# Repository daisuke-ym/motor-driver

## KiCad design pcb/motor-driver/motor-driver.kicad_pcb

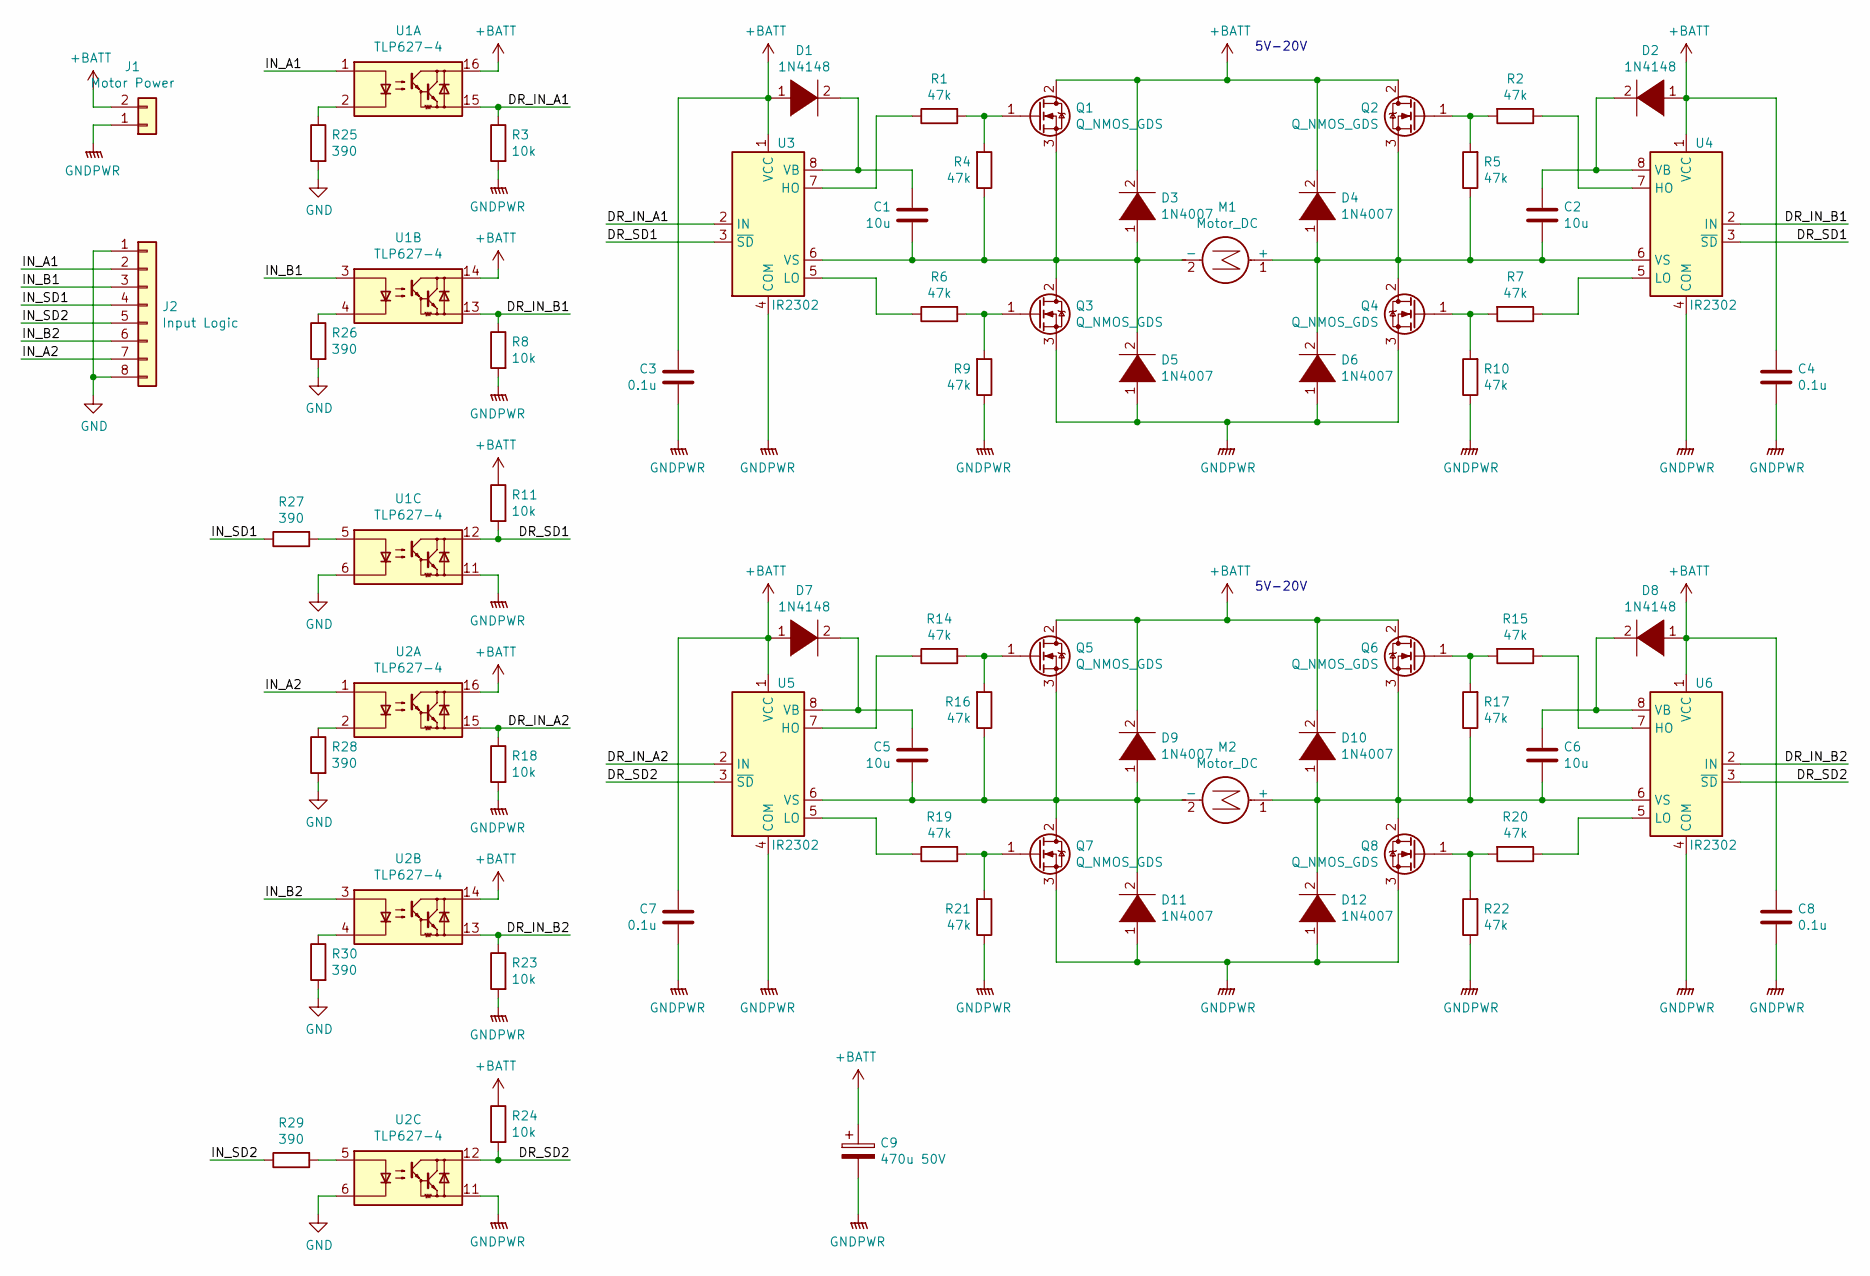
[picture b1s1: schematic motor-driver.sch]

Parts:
C1, C2, C5, C6: 10u; C_Disc_D6.0mm_W4.4mm_P5.00mm
C3, C4, C7, C8: 0.1u; C_Disc_D5.0mm_W2.5mm_P2.50mm
C9: 470u 50V; CP_Radial_D12.5mm_P5.00mm
D1, D2, D7, D8: 1N4148; D_DO-35_SOD27_P2.54mm_Vertical_KathodeUp
D3, D4, D5, D6, D9, D10, D11, D12: 1N4007; D_DO-41_SOD81_P2.54mm_Vertical_KathodeUp
J1: Motor Power; PhoenixContact_MSTBVA_2,5_2-G-5,08_1x02_P5.08mm_Vertical
J2: Input Logic; PinHeader_1x08_P2.54mm_Vertical
M1, M2: Motor_DC; PhoenixContact_MSTBVA_2,5_2-G-5,08_1x02_P5.08mm_Vertical
Q1, Q2, Q3, Q4, Q5, Q6, Q7, Q8: Q_NMOS_GDS; TO-220-3_Vertical
R1, R2, R4, R5, R6, R7, R9, R10, R14, R15, R16, R17, R19, R20, R21, R22: 47k; R_Axial_DIN0207_L6.3mm_D2.5mm_P2.54mm_Vertical
R3, R8, R11, R18, R23, R24: 10k; R_Axial_DIN0207_L6.3mm_D2.5mm_P2.54mm_Vertical
R25, R26, R27, R28, R29, R30: 390; R_Axial_DIN0207_L6.3mm_D2.5mm_P2.54mm_Vertical
U1, U2: TLP627-4; DIP-16_W7.62mm
U3, U4, U5, U6: IR2302; DIP-8_W7.62mm

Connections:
+BATT: C3.1, C4.1, C7.1, C8.1, C9.1, D1.1 (K), D2.1 (K), D3.2 (A), D4.2 (A), D7.1 (K), D8.1 (K), D9.2 (A), D10.2 (A), J1.2, Q1.2 (D), Q2.2 (D), Q5.2 (D), Q6.2 (D), R11.1, R24.1, U1.14, U1.16, U2.14, U2.16, U3.1 (VCC), U4.1 (VCC), U5.1 (VCC), U6.1 (VCC)
/DR_IN_A1: R3.1, U1.15, U3.2 (IN)
/DR_IN_A2: R18.1, U2.15, U5.2 (IN)
/DR_IN_B1: R8.1, U1.13, U4.2 (IN)
/DR_IN_B2: R23.1, U2.13, U6.2 (IN)
/DR_SD1: R11.2, U1.12, U3.3 (~SD), U4.3 (~SD)
/DR_SD2: R24.2, U2.12, U5.3 (~SD), U6.3 (~SD)
/IN_A1: J2.2, U1.1
/IN_A2: J2.7, U2.1
/IN_B1: J2.3, U1.3
/IN_B2: J2.6, U2.3
/IN_SD1: J2.4, R27.1
/IN_SD2: J2.5, R29.1
GND: J2.1, J2.8, R25.2, R26.2, R28.2, R30.2, U1.6, U2.6
GNDPWR: C3.2, C4.2, C7.2, C8.2, C9.2, D5.1 (K), D6.1 (K), D11.1 (K), D12.1 (K), J1.1, Q3.3 (S), Q4.3 (S), Q7.3 (S), Q8.3 (S), R3.2, R8.2, R9.1, R10.1, R18.2, R21.1, R22.1, R23.2, U1.11, U2.11, U3.4 (COM), U4.4 (COM), U5.4 (COM), U6.4 (COM)
unnamed: C1.1, D1.2 (A), U3.8 (VB)
unnamed: C1.2, D3.1 (K), D5.2 (A), M1.2 (-), Q1.3 (S), Q3.2 (D), R4.1, U3.6 (VS)
unnamed: C2.1, D2.2 (A), U4.8 (VB)
unnamed: C2.2, D4.1 (K), D6.2 (A), M1.1 (+), Q2.3 (S), Q4.2 (D), R5.1, U4.6 (VS)
unnamed: C5.1, D7.2 (A), U5.8 (VB)
unnamed: C5.2, D9.1 (K), D11.2 (A), M2.2 (-), Q5.3 (S), Q7.2 (D), R16.1, U5.6 (VS)
unnamed: C6.1, D8.2 (A), U6.8 (VB)
unnamed: C6.2, D10.1 (K), D12.2 (A), M2.1 (+), Q6.3 (S), Q8.2 (D), R17.1, U6.6 (VS)
unnamed: Q1.1 (G), R1.2, R4.2
unnamed: Q2.1 (G), R2.2, R5.2
unnamed: Q3.1 (G), R6.2, R9.2
unnamed: Q4.1 (G), R7.2, R10.2
unnamed: Q5.1 (G), R14.2, R16.2
unnamed: Q6.1 (G), R15.2, R17.2
unnamed: Q7.1 (G), R19.2, R21.2
unnamed: Q8.1 (G), R20.2, R22.2
unnamed: R1.1, U3.7 (HO)
unnamed: R2.1, U4.7 (HO)
unnamed: R6.1, U3.5 (LO)
unnamed: R7.1, U4.5 (LO)
unnamed: R14.1, U5.7 (HO)
unnamed: R15.1, U6.7 (HO)
unnamed: R19.1, U5.5 (LO)
unnamed: R20.1, U6.5 (LO)
unnamed: R25.1, U1.2
unnamed: R26.1, U1.4
unnamed: R27.2, U1.5
unnamed: R28.1, U2.2
unnamed: R29.2, U2.5
unnamed: R30.1, U2.4

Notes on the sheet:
5V-20V

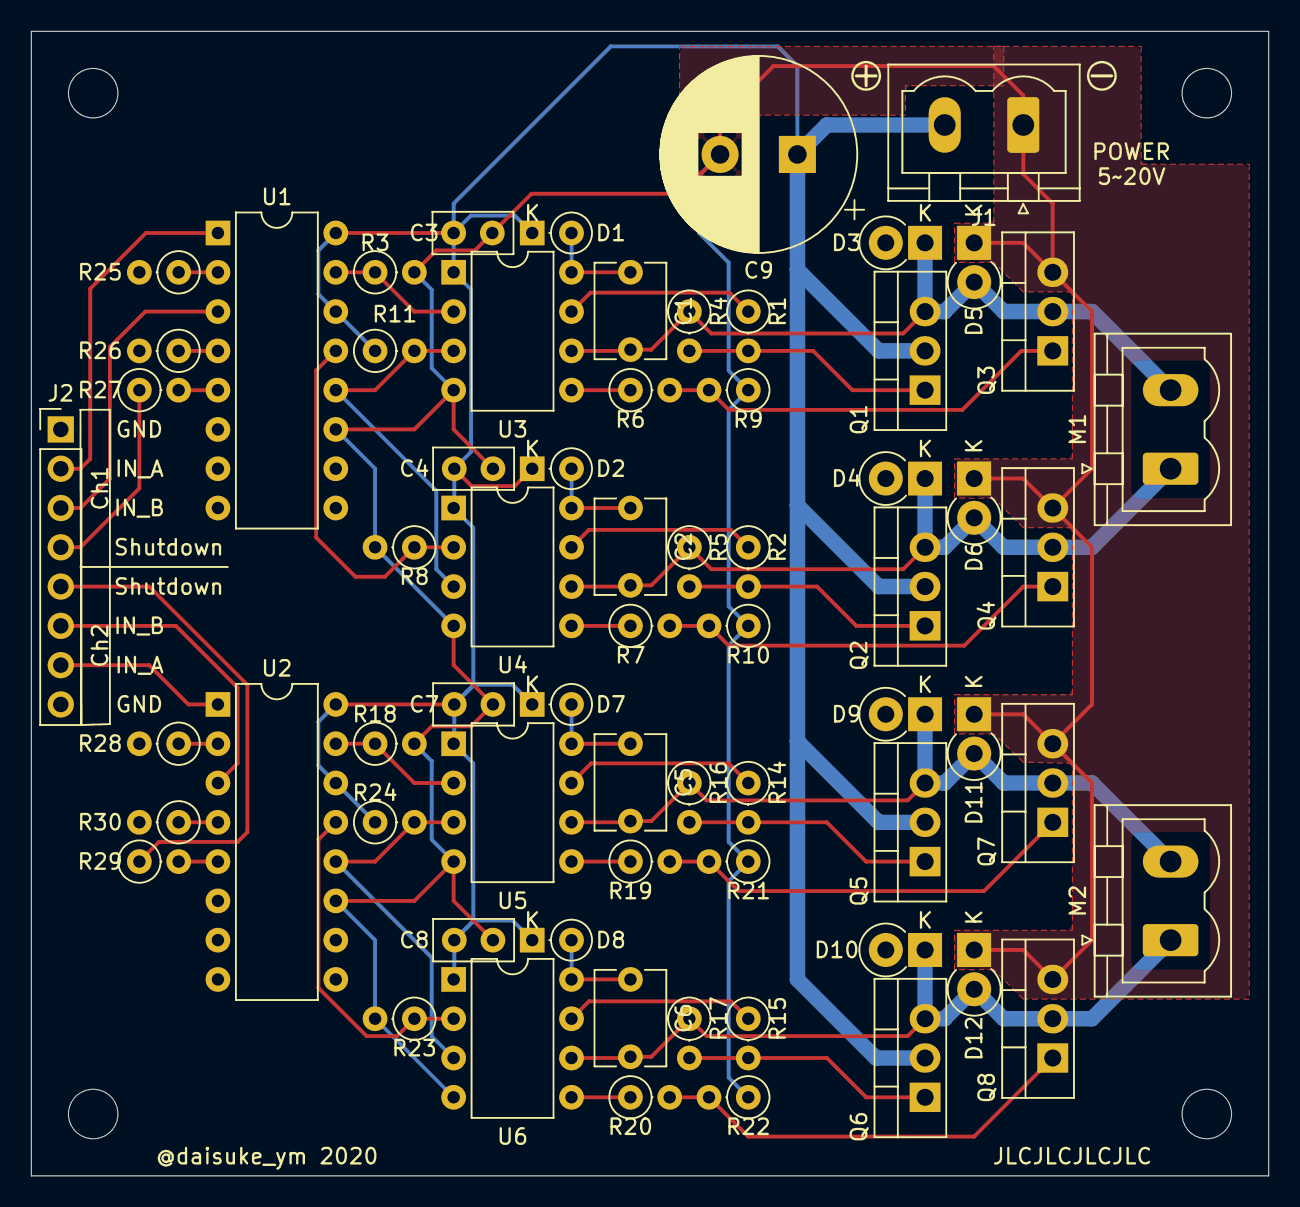
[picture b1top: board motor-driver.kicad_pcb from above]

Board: 2 copper layers, 80.0 x 74.0 mm, 71 parts (0 on the bottom side), 45 nets.

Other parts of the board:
MH1, MH2, MH3, MH4: MountingHole_3.2mm_M3

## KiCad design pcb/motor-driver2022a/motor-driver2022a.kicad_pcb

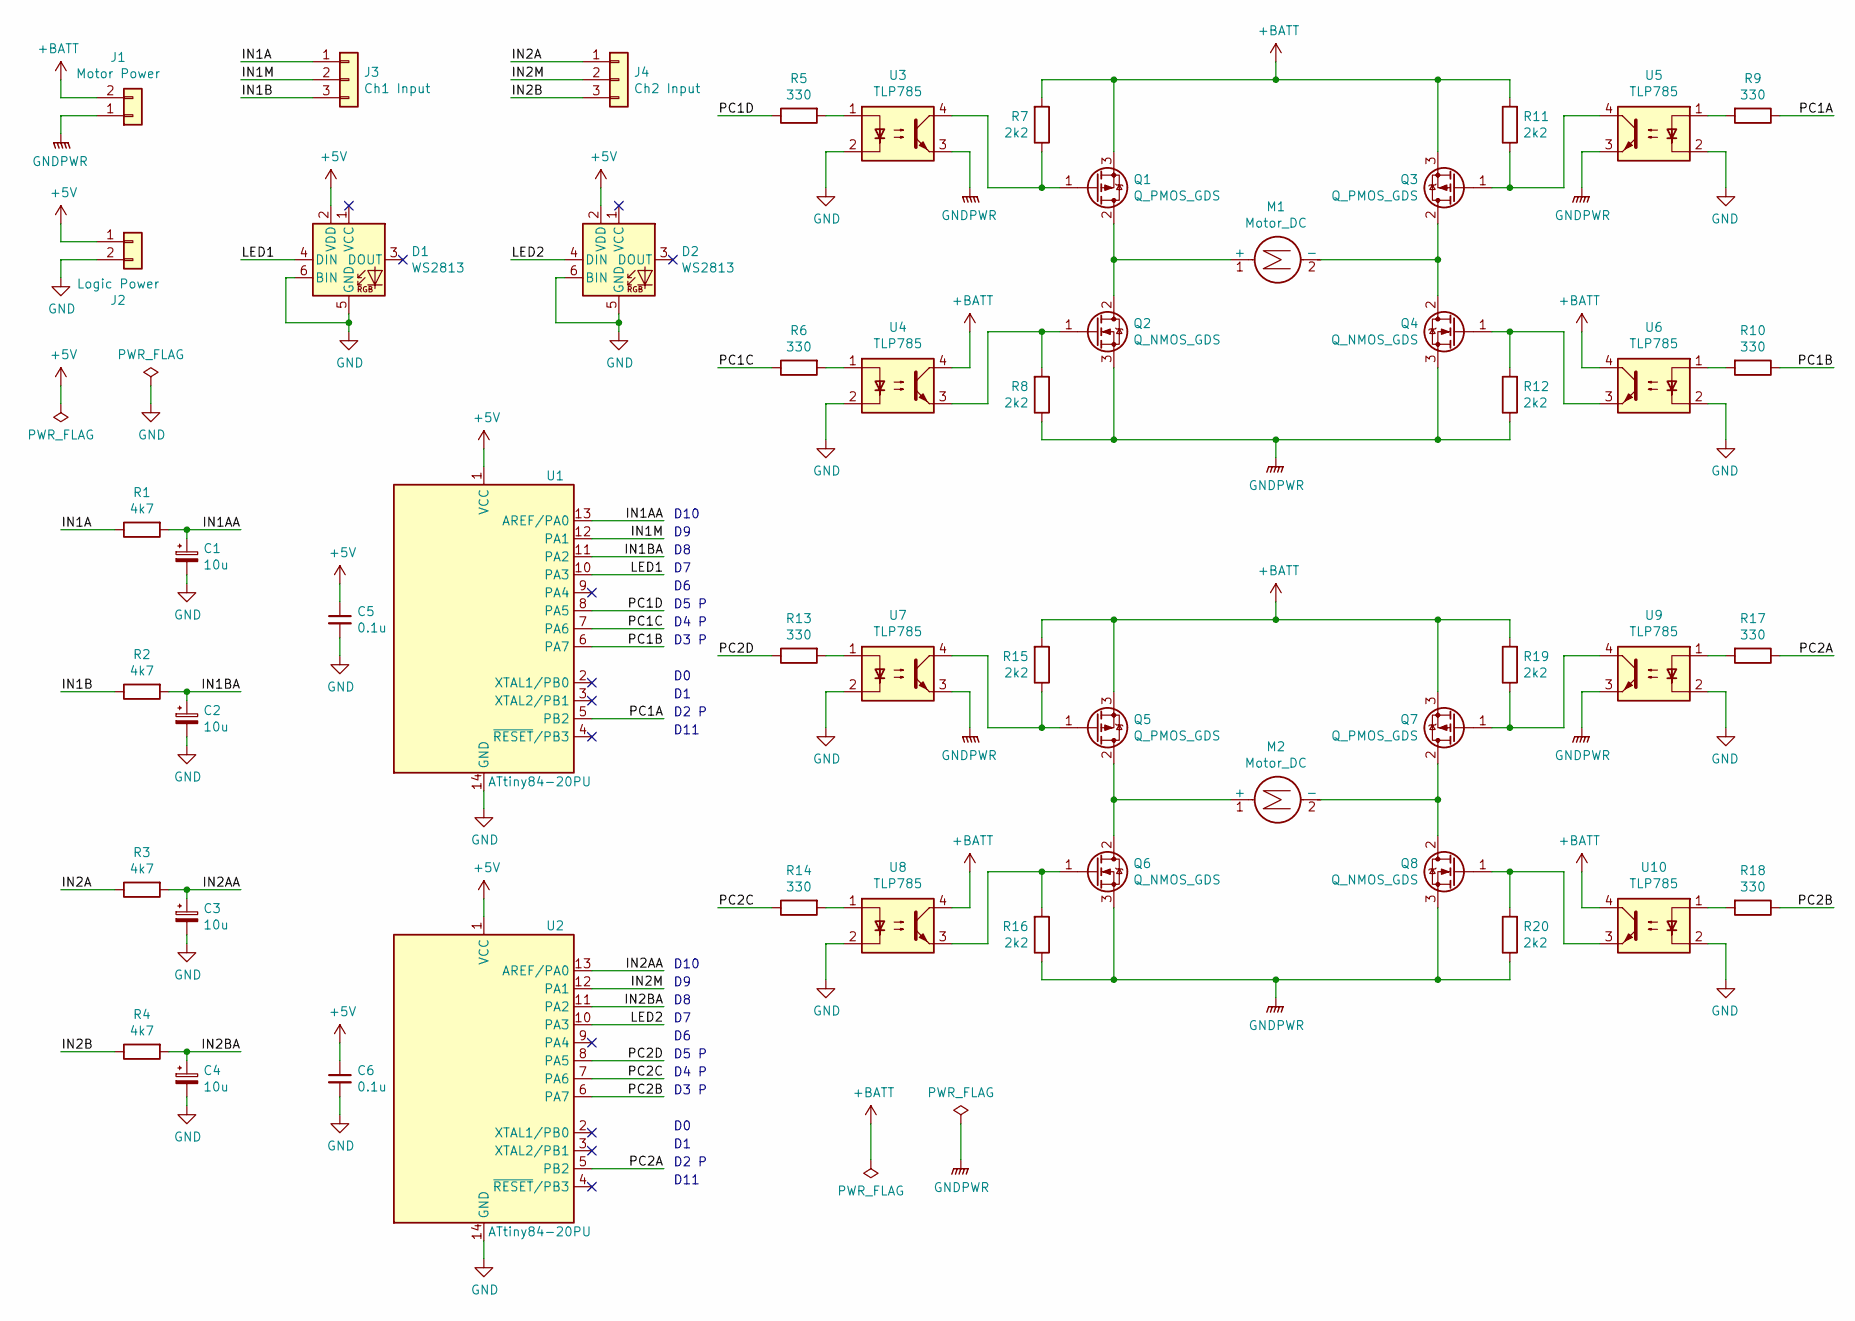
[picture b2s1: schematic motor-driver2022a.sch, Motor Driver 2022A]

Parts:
C1, C2, C3, C4: 10u; CP_Radial_D4.0mm_P1.50mm
C5, C6: 0.1u; C_Disc_D3.0mm_W2.0mm_P2.50mm
D1, D2: WS2813; LED_WS2812_PLCC6_5.0x5.0mm_P1.6mm
J1: Motor Power; AMASS_XT30PW-F_1x02_P2.50mm_Horizontal
J2: Logic Power; PinHeader_1x02_P2.54mm_Horizontal
J3: Ch1 Input; PinHeader_1x03_P2.54mm_Horizontal
J4: Ch2 Input; PinHeader_1x03_P2.54mm_Horizontal
M1, M2: Motor_DC; AMASS_XT30PW-F_1x02_P2.50mm_Horizontal
Q1, Q3, Q5, Q7: Q_PMOS_GDS; TO-220F-3_Vertical
Q2, Q4, Q6, Q8: Q_NMOS_GDS; TO-220F-3_Vertical
R1, R2, R3, R4: 4k7; R_Axial_DIN0207_L6.3mm_D2.5mm_P2.54mm_Vertical
R5, R6, R9, R10, R13, R14, R17, R18: 330; R_Axial_DIN0207_L6.3mm_D2.5mm_P2.54mm_Vertical
R7, R8, R11, R12, R15, R16, R19, R20: 2k2; R_Axial_DIN0207_L6.3mm_D2.5mm_P2.54mm_Vertical
U1, U2: ATtiny84-20PU; DIP-14_W7.62mm
U3, U4, U5, U6, U7, U8, U9, U10: TLP785; DIP-4_W7.62mm

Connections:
+5V: C5.1, C6.1, D1.2 (VDD), D2.2 (VDD), J2.1, U1.1 (VCC), U2.1 (VCC)
+BATT: J1.2, Q1.3 (S), Q3.3 (S), Q5.3 (S), Q7.3 (S), R7.2, R11.2, R15.2, R19.2, U4.4, U6.4, U8.4, U10.4
/IN1A: J3.1, R1.1
/IN1AA: C1.1, R1.2, U1.13 (AREF/PA0)
/IN1B: J3.3, R2.1
/IN1BA: C2.1, R2.2, U1.11 (PA2)
/IN1M: J3.2, U1.12 (PA1)
/IN2A: J4.1, R3.1
/IN2AA: C3.1, R3.2, U2.13 (AREF/PA0)
/IN2B: J4.3, R4.1
/IN2BA: C4.1, R4.2, U2.11 (PA2)
/IN2M: J4.2, U2.12 (PA1)
/LED1: D1.4 (DIN), U1.10 (PA3)
/LED2: D2.4 (DIN), U2.10 (PA3)
/PC1A: R9.1, U1.5 (PB2)
/PC1B: R10.1, U1.6 (PA7)
/PC1C: R6.1, U1.7 (PA6)
/PC1D: R5.1, U1.8 (PA5)
/PC2A: R17.1, U2.5 (PB2)
/PC2B: R18.1, U2.6 (PA7)
/PC2C: R14.1, U2.7 (PA6)
/PC2D: R13.1, U2.8 (PA5)
GND: C1.2, C2.2, C3.2, C4.2, C5.2, C6.2, D1.5 (GND), D1.6 (BIN), D2.5 (GND), D2.6 (BIN), J2.2, U1.14 (GND), U2.14 (GND), U3.2, U4.2, U5.2, U6.2, U7.2, U8.2, U9.2, U10.2
GNDPWR: J1.1, Q2.3 (S), Q4.3 (S), Q6.3 (S), Q8.3 (S), R8.1, R12.1, R16.1, R20.1, U3.3, U5.3, U7.3, U9.3
unnamed: M1.1 (+), Q1.2 (D), Q2.2 (D)
unnamed: M1.2 (-), Q3.2 (D), Q4.2 (D)
unnamed: M2.1 (+), Q5.2 (D), Q6.2 (D)
unnamed: M2.2 (-), Q7.2 (D), Q8.2 (D)
unnamed: Q1.1 (G), R7.1, U3.4
unnamed: Q2.1 (G), R8.2, U4.3
unnamed: Q3.1 (G), R11.1, U5.4
unnamed: Q4.1 (G), R12.2, U6.3
unnamed: Q5.1 (G), R15.1, U7.4
unnamed: Q6.1 (G), R16.2, U8.3
unnamed: Q7.1 (G), R19.1, U9.4
unnamed: Q8.1 (G), R20.2, U10.3
unnamed: R5.2, U3.1
unnamed: R6.2, U4.1
unnamed: R9.2, U5.1
unnamed: R10.2, U6.1
unnamed: R13.2, U7.1
unnamed: R14.2, U8.1
unnamed: R17.2, U9.1
unnamed: R18.2, U10.1

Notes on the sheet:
D10
D4 P
D3 P
D2 P
D5 P
D11

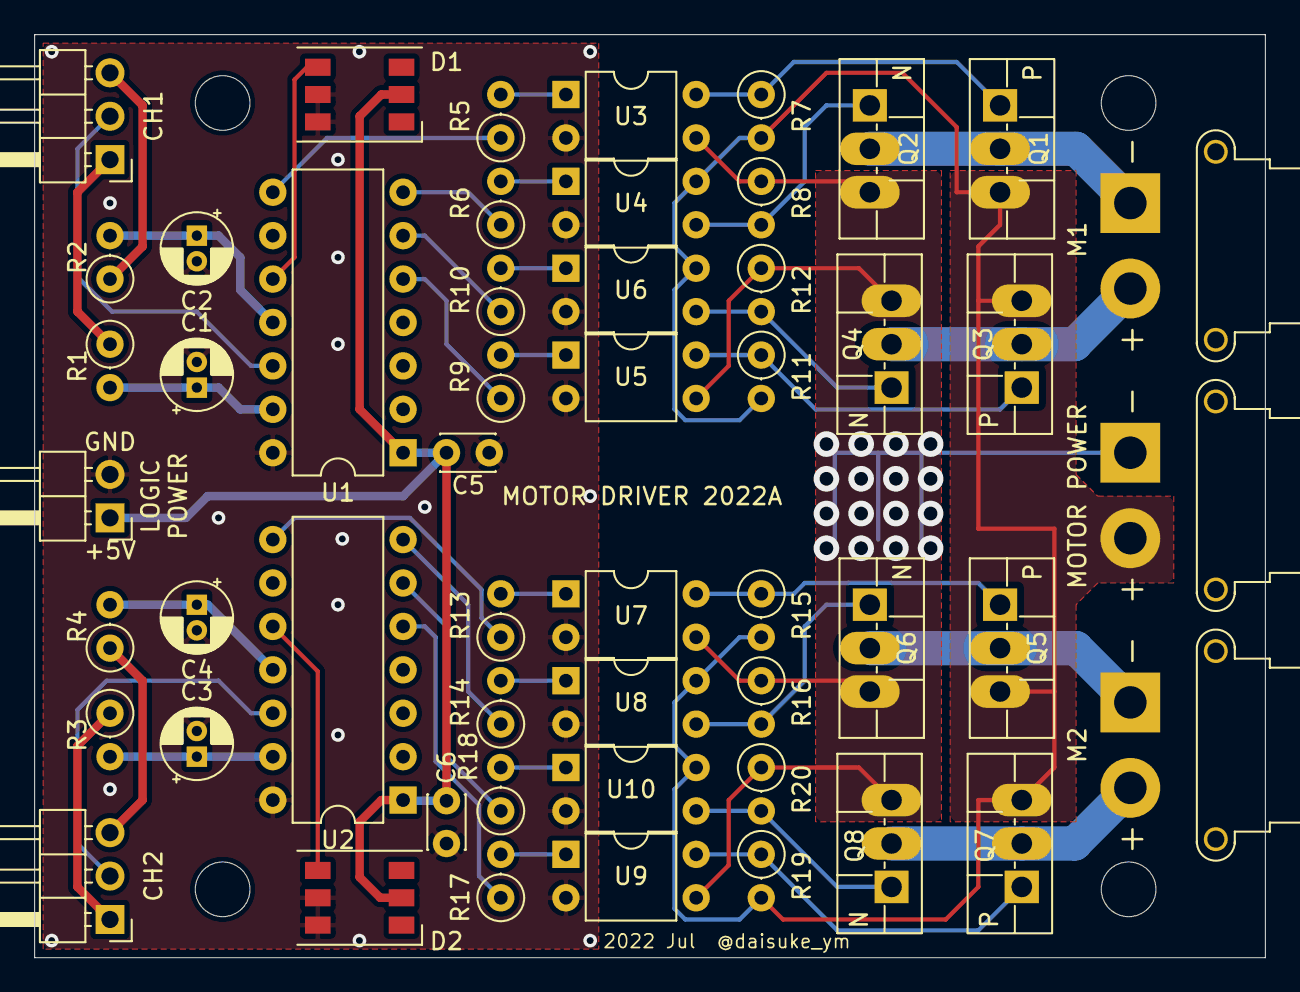
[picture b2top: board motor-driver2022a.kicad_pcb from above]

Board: 2 copper layers, 72.0 x 54.0 mm, 52 parts (0 on the bottom side), 44 nets.

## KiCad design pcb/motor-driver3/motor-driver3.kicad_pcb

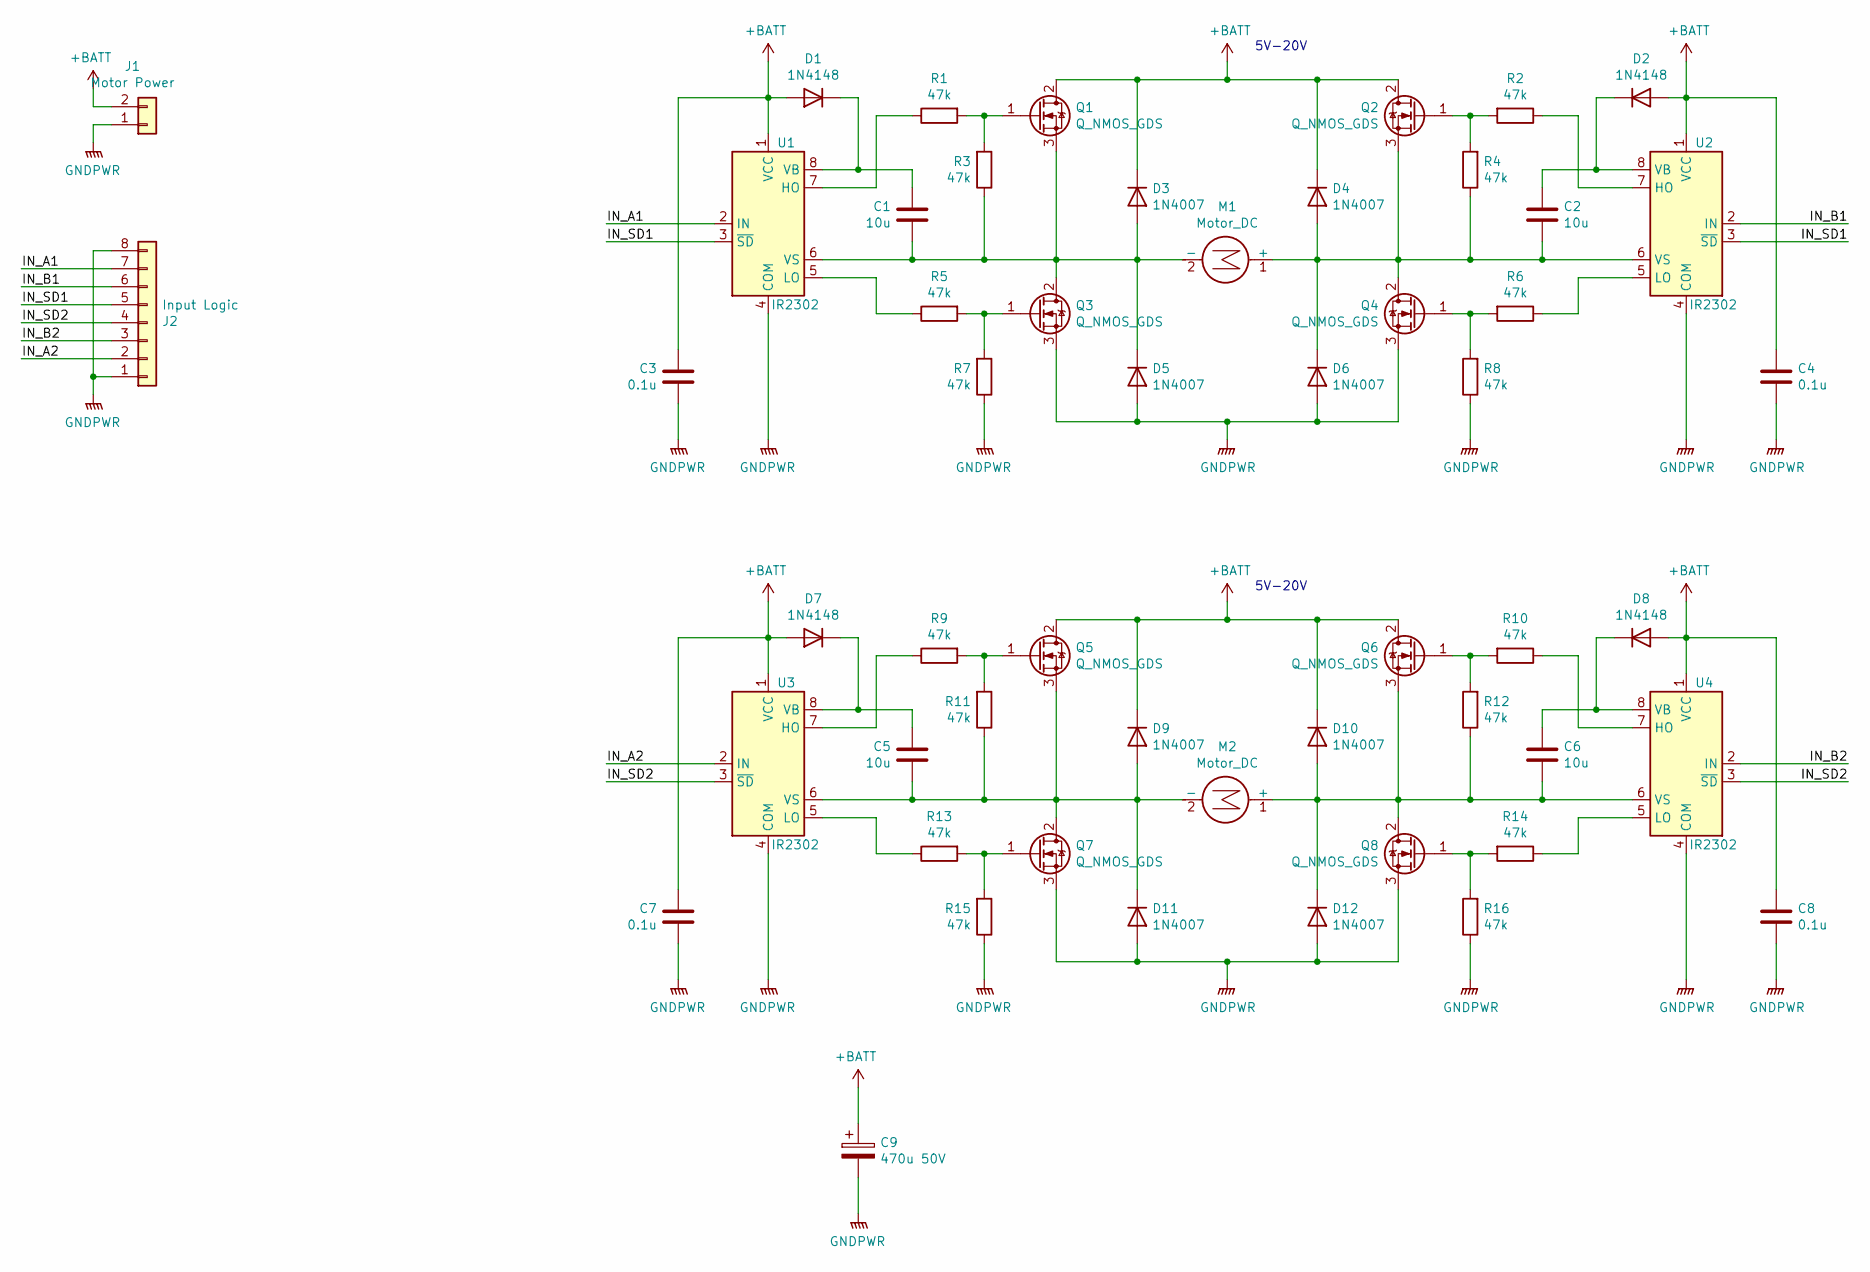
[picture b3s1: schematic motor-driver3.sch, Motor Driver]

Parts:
C1, C2, C5, C6: 10u; C_Disc_D6.0mm_W4.4mm_P5.00mm
C3, C4, C7, C8: 0.1u; C_Rect_L4.0mm_W2.5mm_P2.50mm
C9: 470u 50V; CP_Radial_D12.5mm_P5.00mm
D1, D2, D7, D8: 1N4148; D_DO-35_SOD27_P7.62mm_Horizontal
D3, D4, D5, D6, D9, D10, D11, D12: 1N4007; D_DO-41_SOD81_P10.16mm_Horizontal
J1: Motor Power; JST_VH_B2PS-VH_1x02_P3.96mm_Horizontal
J2: Input Logic; PinHeader_1x08_P2.54mm_Horizontal
M1, M2: Motor_DC; JST_VH_B2PS-VH_1x02_P3.96mm_Horizontal
Q1, Q2, Q3, Q4, Q5, Q6, Q7, Q8: Q_NMOS_GDS; TO-220-3_Horizontal_TabDown
R1, R2, R3, R4, R5, R6, R7, R8, R9, R10, R11, R12, R13, R14, R15, R16: 47k; R_Axial_DIN0207_L6.3mm_D2.5mm_P10.16mm_Horizontal
U1, U2, U3, U4: IR2302; DIP-8_W7.62mm

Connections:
+BATT: C3.1, C4.1, C7.1, C8.1, C9.1, D1.2 (A), D2.2 (A), D3.1 (K), D4.1 (K), D7.2 (A), D8.2 (A), D9.1 (K), D10.1 (K), J1.2, Q1.2 (D), Q2.2 (D), Q5.2 (D), Q6.2 (D), U1.1 (VCC), U2.1 (VCC), U3.1 (VCC), U4.1 (VCC)
/IN_A1: J2.7, U1.2 (IN)
/IN_A2: J2.2, U3.2 (IN)
/IN_B1: J2.6, U2.2 (IN)
/IN_B2: J2.3, U4.2 (IN)
/IN_SD1: J2.5, U1.3 (~SD), U2.3 (~SD)
/IN_SD2: J2.4, U3.3 (~SD), U4.3 (~SD)
GNDPWR: C3.2, C4.2, C7.2, C8.2, C9.2, D5.2 (A), D6.2 (A), D11.2 (A), D12.2 (A), J1.1, J2.1, J2.8, Q3.3 (S), Q4.3 (S), Q7.3 (S), Q8.3 (S), R7.1, R8.1, R15.1, R16.1, U1.4 (COM), U2.4 (COM), U3.4 (COM), U4.4 (COM)
unnamed: C1.1, D1.1 (K), U1.8 (VB)
unnamed: C1.2, D3.2 (A), D5.1 (K), M1.2 (-), Q1.3 (S), Q3.2 (D), R3.1, U1.6 (VS)
unnamed: C2.1, D2.1 (K), U2.8 (VB)
unnamed: C2.2, D4.2 (A), D6.1 (K), M1.1 (+), Q2.3 (S), Q4.2 (D), R4.1, U2.6 (VS)
unnamed: C5.1, D7.1 (K), U3.8 (VB)
unnamed: C5.2, D9.2 (A), D11.1 (K), M2.2 (-), Q5.3 (S), Q7.2 (D), R11.1, U3.6 (VS)
unnamed: C6.1, D8.1 (K), U4.8 (VB)
unnamed: C6.2, D10.2 (A), D12.1 (K), M2.1 (+), Q6.3 (S), Q8.2 (D), R12.1, U4.6 (VS)
unnamed: Q1.1 (G), R1.2, R3.2
unnamed: Q2.1 (G), R2.2, R4.2
unnamed: Q3.1 (G), R5.2, R7.2
unnamed: Q4.1 (G), R6.2, R8.2
unnamed: Q5.1 (G), R9.2, R11.2
unnamed: Q6.1 (G), R10.2, R12.2
unnamed: Q7.1 (G), R13.2, R15.2
unnamed: Q8.1 (G), R14.2, R16.2
unnamed: R1.1, U1.7 (HO)
unnamed: R2.1, U2.7 (HO)
unnamed: R5.1, U1.5 (LO)
unnamed: R6.1, U2.5 (LO)
unnamed: R9.1, U3.7 (HO)
unnamed: R10.1, U4.7 (HO)
unnamed: R13.1, U3.5 (LO)
unnamed: R14.1, U4.5 (LO)

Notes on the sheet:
5V-20V

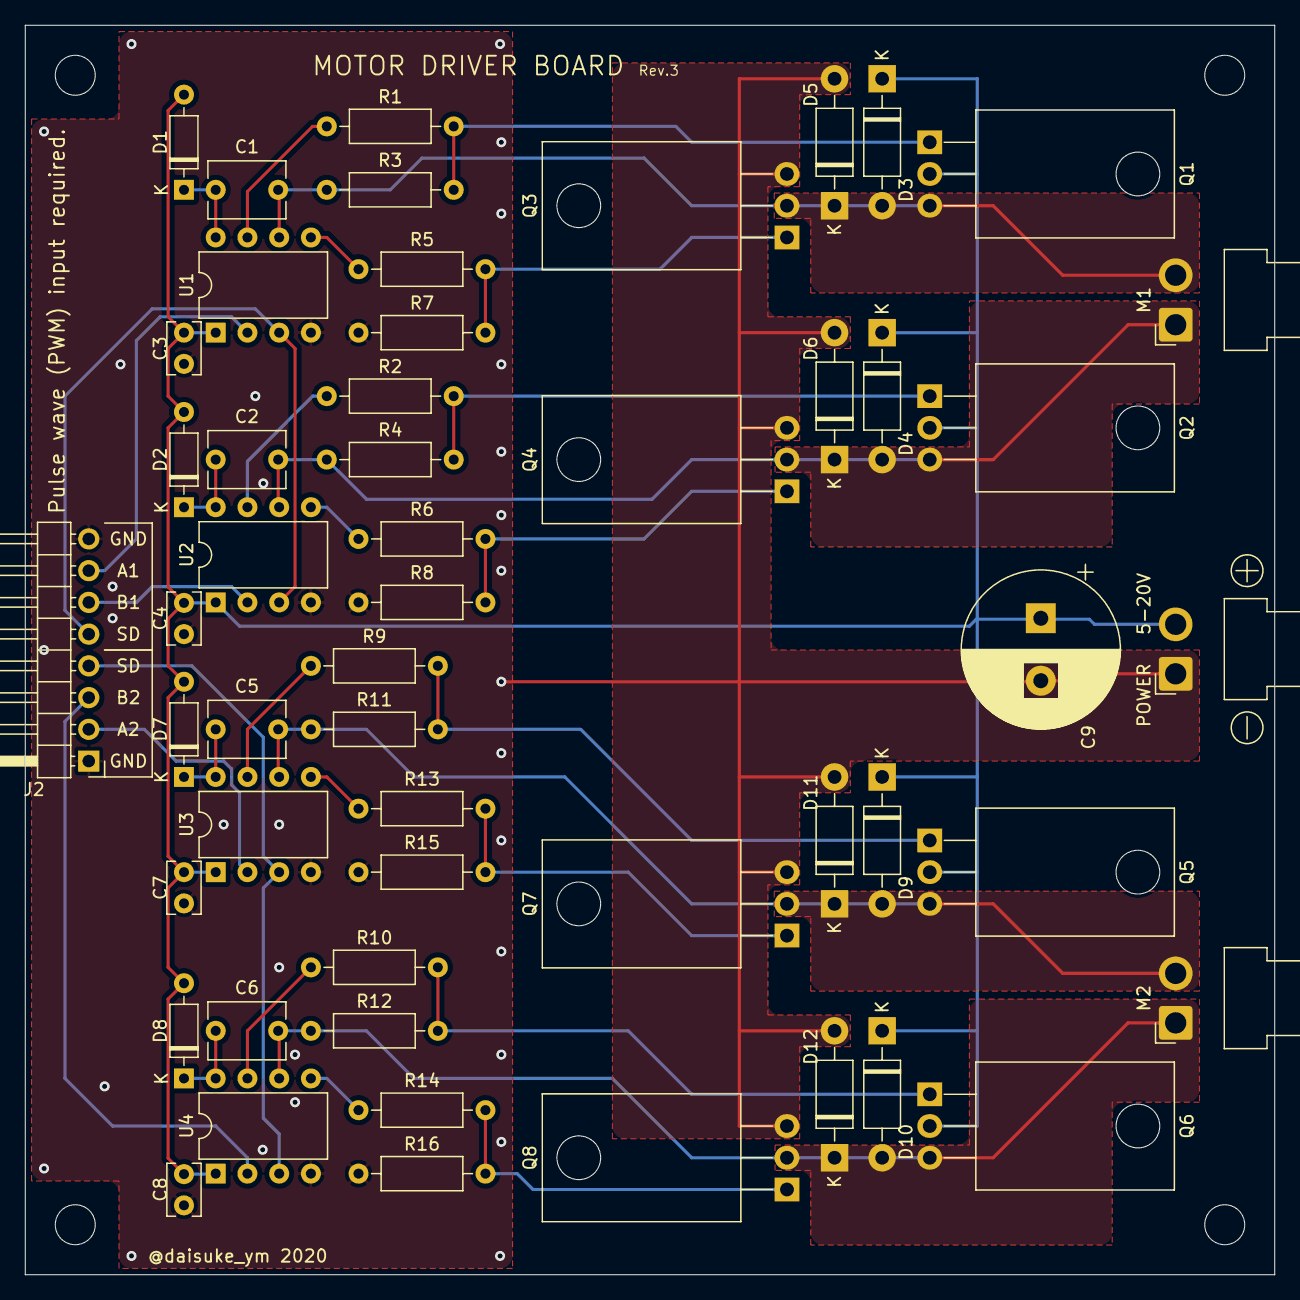
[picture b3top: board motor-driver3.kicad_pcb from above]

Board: 2 copper layers, 100.0 x 100.0 mm, 57 parts (0 on the bottom side), 32 nets.

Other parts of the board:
MH1, MH2, MH3, MH4: MountingHole_3.2mm_M3

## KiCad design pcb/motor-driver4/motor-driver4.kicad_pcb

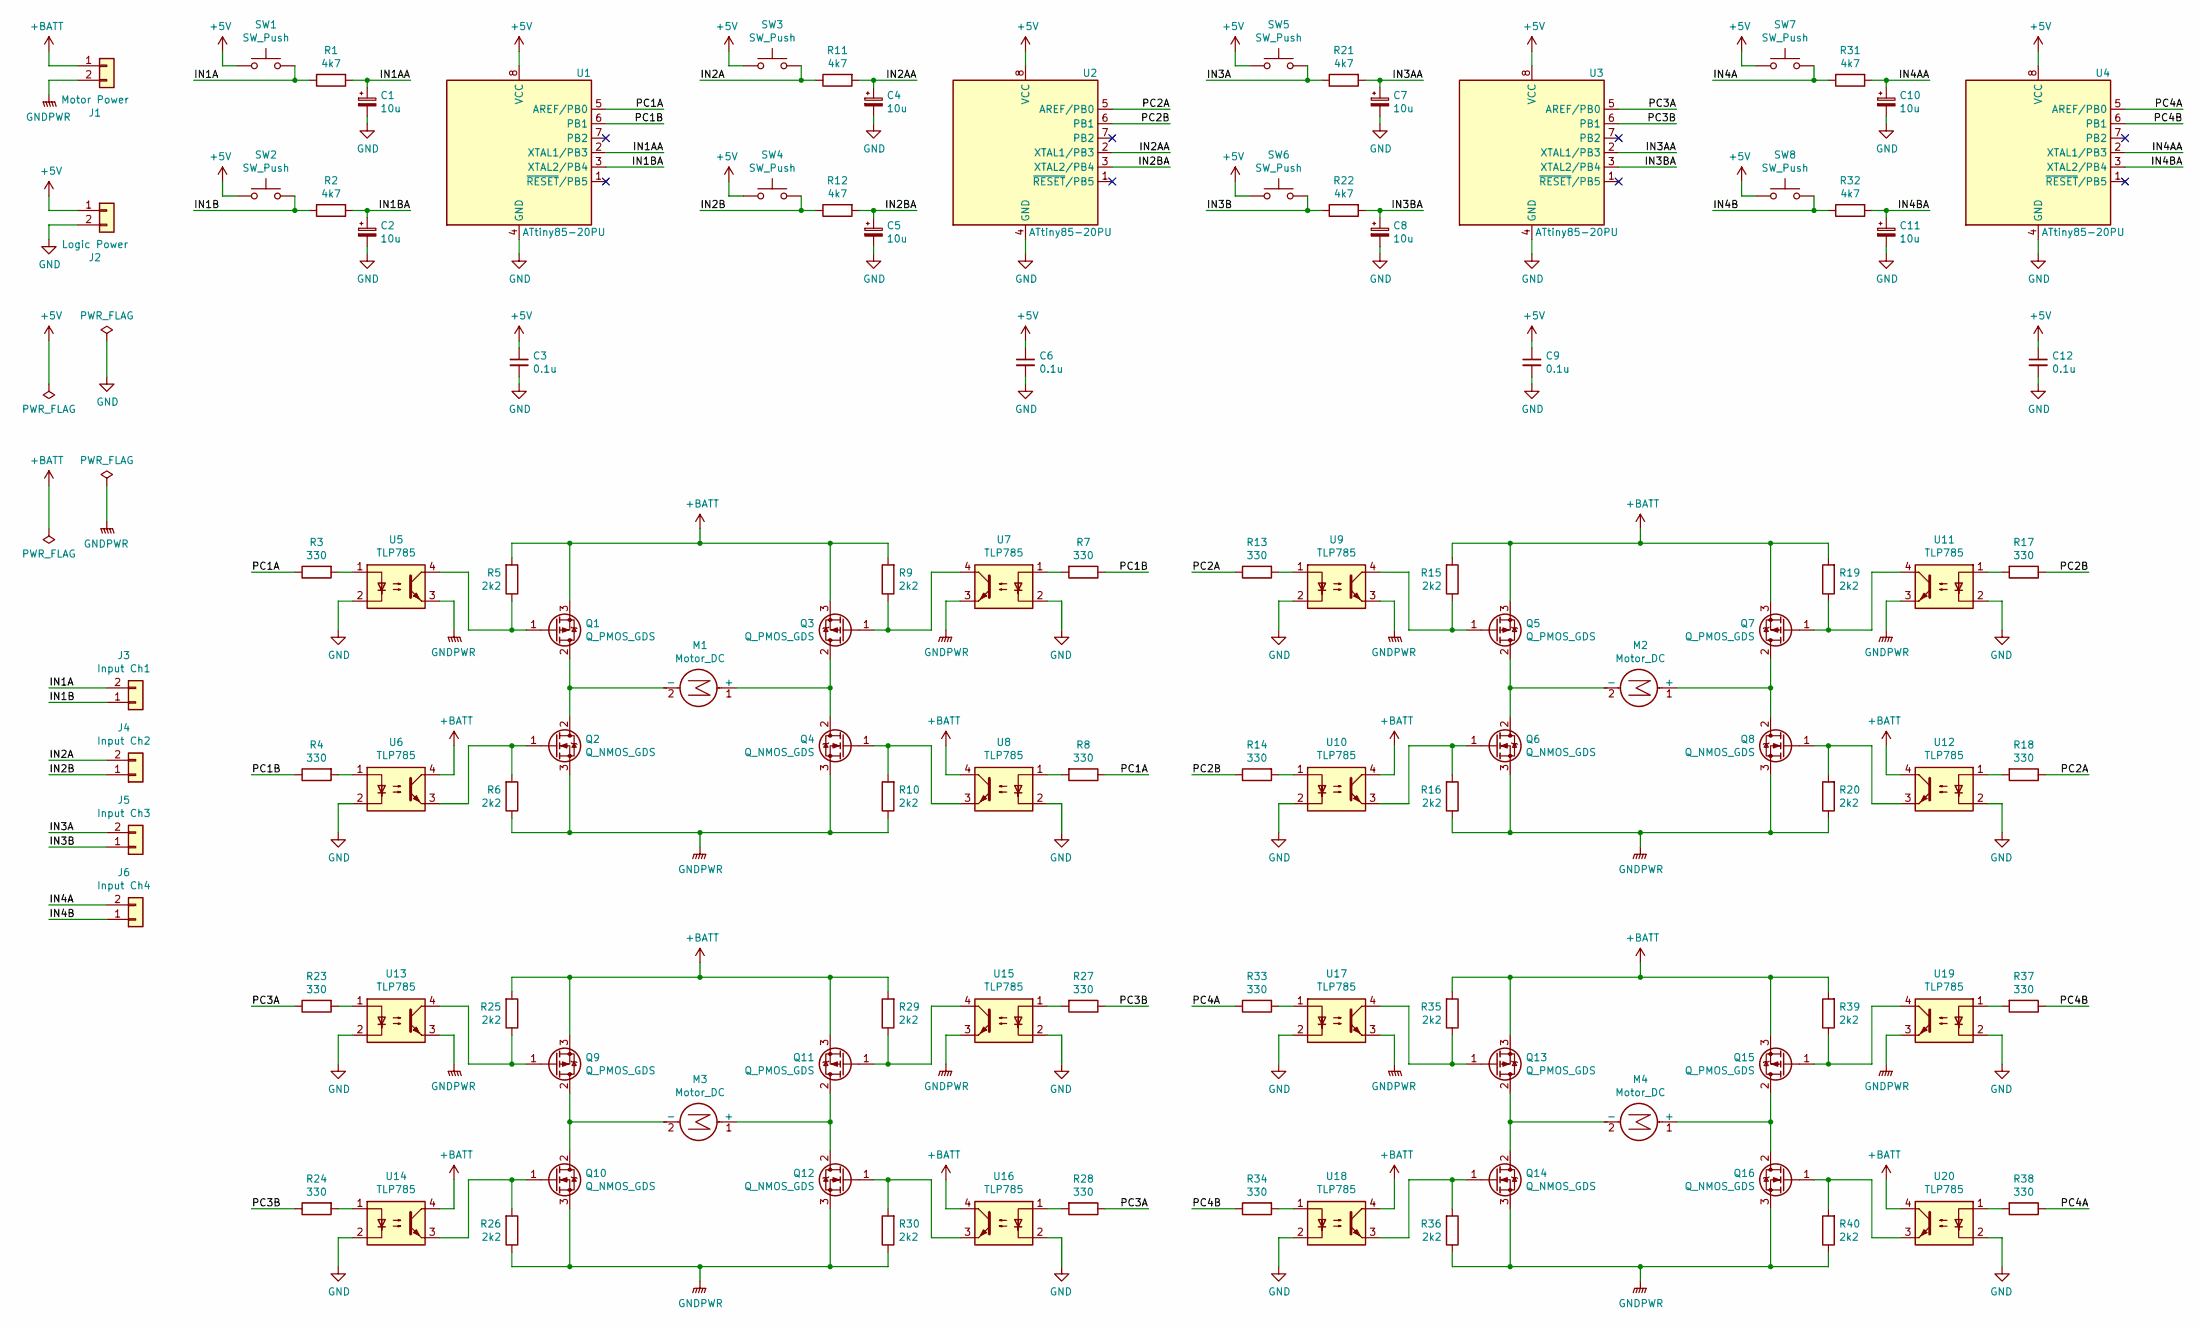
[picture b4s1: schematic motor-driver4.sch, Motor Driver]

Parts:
C1, C2, C4, C5, C7, C8, C10, C11: 10u; CP_Radial_D4.0mm_P1.50mm
C3, C6, C9, C12: 0.1u; C_Disc_D3.4mm_W2.1mm_P2.50mm
J1: Motor Power; JST_VH_B2PS-VH_1x02_P3.96mm_Horizontal
J2: Logic Power; PinHeader_1x02_P2.54mm_Horizontal
J3: Input Ch1; PinHeader_1x02_P2.54mm_Horizontal
J4: Input Ch2; PinHeader_1x02_P2.54mm_Horizontal
J5: Input Ch3; PinHeader_1x02_P2.54mm_Horizontal
J6: Input Ch4; PinHeader_1x02_P2.54mm_Horizontal
M1, M2, M3, M4: Motor_DC; JST_VH_B2PS-VH_1x02_P3.96mm_Horizontal
Q1, Q3, Q5, Q7, Q9, Q11, Q13, Q15: Q_PMOS_GDS; TO-220-3_Horizontal_TabDown
Q2, Q4, Q6, Q8, Q10, Q12, Q14, Q16: Q_NMOS_GDS; TO-220-3_Horizontal_TabDown
R1, R2, R11, R12, R21, R22, R31, R32: 4k7; R_Axial_DIN0207_L6.3mm_D2.5mm_P10.16mm_Horizontal
R3, R4, R7, R8, R13, R14, R17, R18, R23, R24, R27, R28, R33, R34, R37, R38: 330; R_Axial_DIN0207_L6.3mm_D2.5mm_P10.16mm_Horizontal
R5, R6, R9, R10, R15, R16, R19, R20, R25, R26, R29, R30, R35, R36, R39, R40: 2k2; R_Axial_DIN0207_L6.3mm_D2.5mm_P10.16mm_Horizontal
SW1, SW2, SW3, SW4, SW5, SW6, SW7, SW8: SW_Push; TactSW_TVBP06_3.5x6.0-ThroughHole
U1, U2, U3, U4: ATtiny85-20PU; DIP-8_W7.62mm
U5, U6, U7, U8, U9, U10, U11, U12, U13, U14, U15, U16, U17, U18, U19, U20: TLP785; DIP-4_W7.62mm

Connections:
+5V: C3.1, C6.1, C9.1, C12.1, J2.1, SW1.2, SW2.2, SW3.2, SW4.2, SW5.2, SW6.2, SW7.2, SW8.2, U1.8 (VCC), U2.8 (VCC), U3.8 (VCC), U4.8 (VCC)
+BATT: J1.1, Q1.3 (S), Q3.3 (S), Q5.3 (S), Q7.3 (S), Q9.3 (S), Q11.3 (S), Q13.3 (S), Q15.3 (S), R5.2, R9.2, R15.2, R19.2, R25.2, R29.2, R35.2, R39.2, U6.4, U8.4, U10.4, U12.4, U14.4, U16.4, U18.4, U20.4
/IN1A: J3.2, R1.1, SW1.1
/IN1AA: C1.1, R1.2, U1.2 (XTAL1/PB3)
/IN1B: J3.1, R2.1, SW2.1
/IN1BA: C2.1, R2.2, U1.3 (XTAL2/PB4)
/IN2A: J4.2, R11.1, SW3.1
/IN2AA: C4.1, R11.2, U2.2 (XTAL1/PB3)
/IN2B: J4.1, R12.1, SW4.1
/IN2BA: C5.1, R12.2, U2.3 (XTAL2/PB4)
/IN3A: J5.2, R21.1, SW5.1
/IN3AA: C7.1, R21.2, U3.2 (XTAL1/PB3)
/IN3B: J5.1, R22.1, SW6.1
/IN3BA: C8.1, R22.2, U3.3 (XTAL2/PB4)
/IN4A: J6.2, R31.1, SW7.1
/IN4AA: C10.1, R31.2, U4.2 (XTAL1/PB3)
/IN4B: J6.1, R32.1, SW8.1
/IN4BA: C11.1, R32.2, U4.3 (XTAL2/PB4)
/PC1A: R3.1, R8.1, U1.5 (AREF/PB0)
/PC1B: R4.1, R7.1, U1.6 (PB1)
/PC2A: R13.1, R18.1, U2.5 (AREF/PB0)
/PC2B: R14.1, R17.1, U2.6 (PB1)
/PC3A: R23.1, R28.1, U3.5 (AREF/PB0)
/PC3B: R24.1, R27.1, U3.6 (PB1)
/PC4A: R33.1, R38.1, U4.5 (AREF/PB0)
/PC4B: R34.1, R37.1, U4.6 (PB1)
GND: C1.2, C2.2, C3.2, C4.2, C5.2, C6.2, C7.2, C8.2, C9.2, C10.2, C11.2, C12.2, J2.2, U1.4 (GND), U2.4 (GND), U3.4 (GND), U4.4 (GND), U5.2, U6.2, U7.2, U8.2, U9.2, U10.2, U11.2, U12.2, U13.2, U14.2, U15.2, U16.2, U17.2, U18.2, U19.2, U20.2
GNDPWR: J1.2, Q2.3 (S), Q4.3 (S), Q6.3 (S), Q8.3 (S), Q10.3 (S), Q12.3 (S), Q14.3 (S), Q16.3 (S), R6.1, R10.1, R16.1, R20.1, R26.1, R30.1, R36.1, R40.1, U5.3, U7.3, U9.3, U11.3, U13.3, U15.3, U17.3, U19.3
unnamed: M1.1 (+), Q3.2 (D), Q4.2 (D)
unnamed: M1.2 (-), Q1.2 (D), Q2.2 (D)
unnamed: M2.1 (+), Q7.2 (D), Q8.2 (D)
unnamed: M2.2 (-), Q5.2 (D), Q6.2 (D)
unnamed: M3.1 (+), Q11.2 (D), Q12.2 (D)
unnamed: M3.2 (-), Q9.2 (D), Q10.2 (D)
unnamed: M4.1 (+), Q15.2 (D), Q16.2 (D)
unnamed: M4.2 (-), Q13.2 (D), Q14.2 (D)
unnamed: Q1.1 (G), R5.1, U5.4
unnamed: Q2.1 (G), R6.2, U6.3
unnamed: Q3.1 (G), R9.1, U7.4
unnamed: Q4.1 (G), R10.2, U8.3
unnamed: Q5.1 (G), R15.1, U9.4
unnamed: Q6.1 (G), R16.2, U10.3
unnamed: Q7.1 (G), R19.1, U11.4
unnamed: Q8.1 (G), R20.2, U12.3
unnamed: Q9.1 (G), R25.1, U13.4
unnamed: Q10.1 (G), R26.2, U14.3
unnamed: Q11.1 (G), R29.1, U15.4
unnamed: Q12.1 (G), R30.2, U16.3
unnamed: Q13.1 (G), R35.1, U17.4
unnamed: Q14.1 (G), R36.2, U18.3
unnamed: Q15.1 (G), R39.1, U19.4
unnamed: Q16.1 (G), R40.2, U20.3
unnamed: R3.2, U5.1
unnamed: R4.2, U6.1
unnamed: R7.2, U7.1
unnamed: R8.2, U8.1
unnamed: R13.2, U9.1
unnamed: R14.2, U10.1
unnamed: R17.2, U11.1
unnamed: R18.2, U12.1
unnamed: R23.2, U13.1
unnamed: R24.2, U14.1
unnamed: R27.2, U15.1
unnamed: R28.2, U16.1
unnamed: R33.2, U17.1
unnamed: R34.2, U18.1
unnamed: R37.2, U19.1
unnamed: R38.2, U20.1
